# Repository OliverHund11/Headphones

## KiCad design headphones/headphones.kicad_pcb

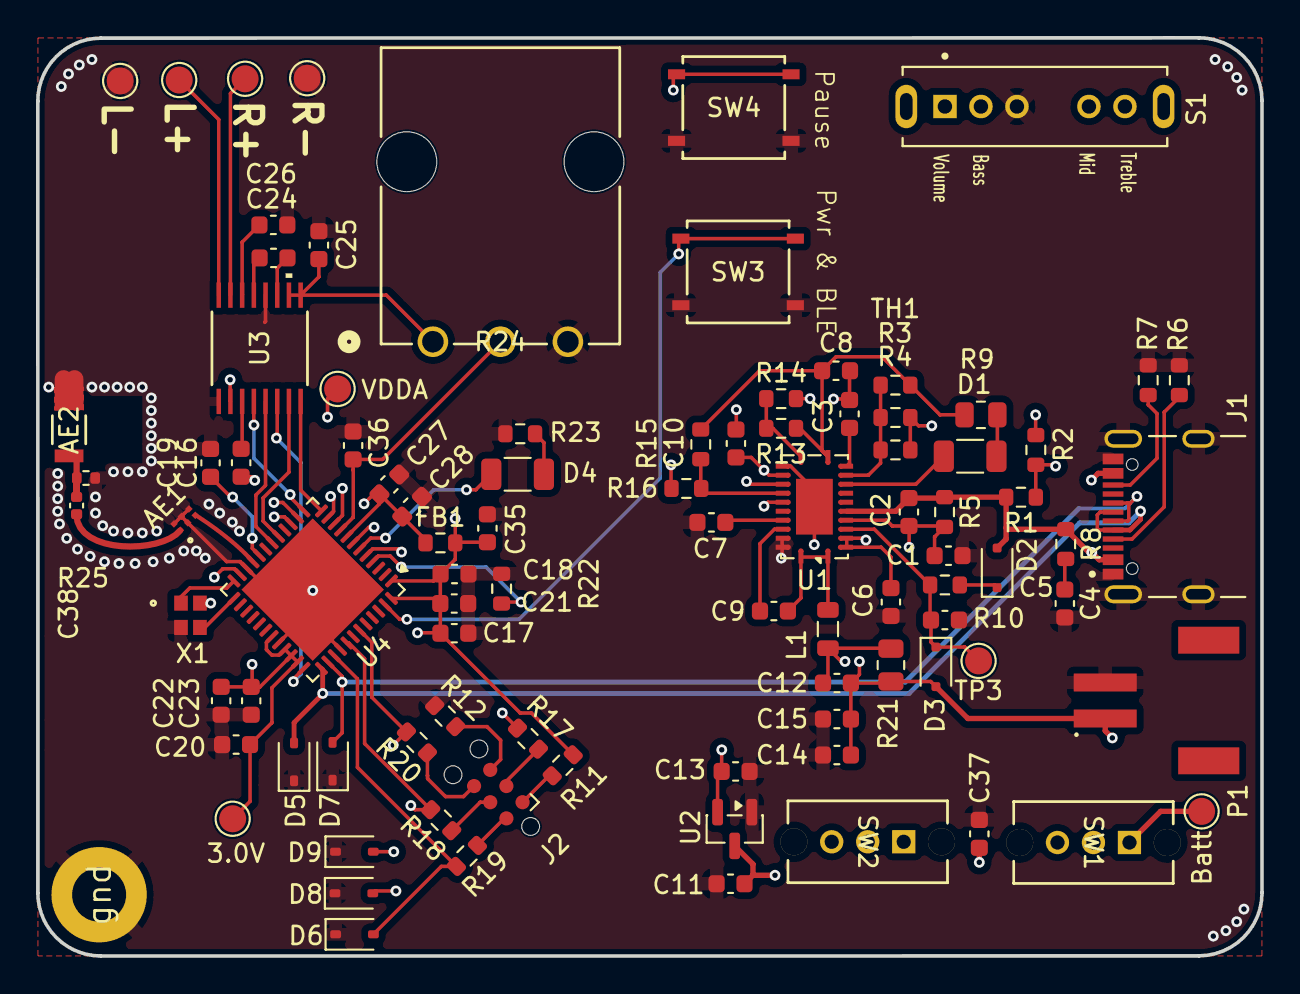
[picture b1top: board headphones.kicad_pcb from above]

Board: 4 copper layers, 68.0 x 51.0 mm, 93 parts (0 on the bottom side), 64 nets.

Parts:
3.0V: TestPoint; TestPoint_Pad_D1.5mm
AE1: MLPF-WB55-01E3; MLPF-WB55-01E3_STM
AE2: 2119640001; ANT_211964-0001_MOL
Batt: TestPoint; TestPoint_Pad_D1.5mm
C1, C2, C5, C10, C12: 0.1uF; C_0603_1608Metric
C3: 33nF; C_0603_1608Metric
C4, C16: 2.2uF; C_0603_1608Metric
C6, C14, C15: 10uF; C_0603_1608Metric
C7, C8, C11, C13, C37: 1uF; C_0603_1608Metric
C9: 0.047uF; C_0603_1608Metric
C17: 10u; C_0603_1608Metric
C18, C19, C20, C21, C22, C23, C36: 0.1u; C_0603_1608Metric
C24: 220nF; C_0603_1608Metric
C25, C26: 4.7uF; C_0603_1608Metric
C27: 10n; C_0603_1608Metric
C28, C35: 1u; C_0603_1608Metric
C38: 2.7pF; C_0402_1005Metric
D1: LED, R; R_1206_3216Metric
D2, D3: D_SOD-323F
D4: LED, O; R_1206_3216Metric
D5, D6, D7, D8, D9: SD03CQ_SOD323; D_SOD-323
FB1: 120R; R_0603_1608Metric
J1: UJ20-C-H-G-SMT-1-P16-TR; SAMESKY_UJ20-C-H-G-SMT-1-P16-TR
J2: Conn_ARM_SWD_TagConnect_TC2030-NL; Tag-Connect_TC2030-IDC-NL_2x03_P1.27mm_Vertical
L1: 10uH; L_0805_2012Metric
P1: S2B-PH-SM4-TB
R1: 47k; R_0603_1608Metric
R2: 15k; R_0603_1608Metric
R3, R6, R7: 5.1k; R_0603_1608Metric
R4: 30k; R_0603_1608Metric
R5: 20m; R_0603_1608Metric
R8: 2; R_0603_1608Metric
R9: 750; R_0805_2012Metric
R10: 5; R_0603_1608Metric
R11, R12, R17, R18, R19, R20: 150; R_0603_1608Metric
R13: 13k; R_0603_1608Metric
R14: 1k; R_0603_1608Metric
R15: 8.2k; R_0603_1608Metric
R16: 56k; R_0603_1608Metric
R21: 47m; R_0805_2012Metric
R22: 10k; R_0603_1608Metric
R23: 330; R_0603_1608Metric
R24: P120PK-Y25BR10K; POT_P120PK-x25_TTE
R25: 0; R_0402_1005Metric
S1: SLW-1478144-5A-S-D; SW_SLW-1478144-5A-S-D
SW1, SW2: OS102011MS2QN1; SPDT_OS102011_CNK
SW3, SW4: SW_MEC_5E; SON4_PTS526 SM15 SMTR2 LFS_CNK
TH1: 10k; R_0603_1608Metric
TP3: TestPoint; TestPoint_Pad_D1.5mm
TP8: +LDriver; TestPoint_Pad_D1.5mm
TP9: -LDriver; TestPoint_Pad_D1.5mm
TP10: +RDriver; TestPoint_Pad_D1.5mm
TP11: -RDriver; TestPoint_Pad_D1.5mm
U1: BQ24133RGY; Texas_RGY_R-PVQFN-N24_EP2.05x3.1mm
U2: AP2127N-3.0; SOT-23
U3: NAU8402WG; TSSOP16_NAU8402_NUV
U4: STM32WB55CCUx; QFN-48-1EP_7x7mm_P0.5mm_EP5.6x5.6mm
VDDA: TestPoint; TestPoint_Pad_D1.5mm
X1: NX2016SA-32MHZ-EXS00A-CS06654; NX2016SA_NDK
gnd: (no value)

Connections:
+3.0V: 3.0V.1 (1_1), C13.2, C17.1, C18.1, C19.1, C20.1, C21.1, C22.1, C23.1, C25.1, C35.1, FB1.2, R11.2, R24.1, U2.2 (VO), U3.9 (VDDB), U3.10 (LINEVDD), U4.1 (VBAT), U4.20 (VDD), U4.23 (VDDRF), U4.31 (VFBSMPS), U4.33 (VLXSMPS), U4.34 (VDDSMPS), U4.35 (VDD), U4.48 (VDD)
+3.3V, ref: C8.2, R3.1, R9.2, R13.1, R15.1, U1.12 (VREF)
+5V: C2.1, D2.2 (A), J1.A4_B9 (VBUS), J1.B4_A9 (VBUS__1), R1.1, R5.1, R8.1, SW1.3, U1.6 (ACP)
+BATT: Batt.1 (1_1), C10.2, C12.2, C14.2, C15.2, D3.2 (A), P1.1, R21.2, SW1.1, U1.15 (SRN)
/Bass: S1.2, U4.11 (PA2)
/D+: D7.2 (A2), J1.A6 (DP1), J1.B6 (DP2), U4.38 (PA12)
/D-: D5.2 (A2), J1.A7 (DN1), J1.B7 (DN2), U4.37 (PA11)
/Lsig: TP8.1 (1_1), U3.16 (LLINEOU)
/Mid: S1.5, U4.14 (PA5)
/Mute: U3.4 (MUTEB), U4.13 (PA4)
/NRST: R17.2, U4.7 (NRST)
/PVCC: C1.1, C2.2, C6.1, R5.2, U1.2 (PVCC), U1.3 (PVCC), U1.5 (ACN)
/Rsig: TP10.1 (1_1), U3.15 (RLINEOUT)
/SAI_FS: U3.5 (FS), U4.18 (PA9)
/SAI_MCLK: U3.8 (MCLK), U4.12 (PA3)
/SAI_SCK: U3.7 (BCLK), U4.17 (PA8)
/SAI_SD: U3.6 (DACIN), U4.36 (PA10)
/SWCLK: D8.2 (A2), R18.2, U4.41 (PA14)
/SWDIO: D6.2 (A2), R19.2, U4.39 (PA13)
/SWO: D9.2 (A2), R20.2, U4.43 (PB3)
/Treble: S1.6, U4.15 (PA6)
/Volume: S1.1, U4.10 (PA1)
GND: AE1.A2 (GND4), AE1.B1 (GND3), AE1.B2 (GND2), AE1.B3 (GND1), AE2.2, C1.2, C4.2, C5.2, C6.2, C7.1, C11.1, C13.1, C14.1, C15.1, C16.1, C17.2, C18.2, C19.2, C20.2, C21.2, C22.2, C23.2, C25.2, C26.2, C27.2, C28.2, C35.2, C36.2, C37.1, D5.1 (A1), D6.1 (A1), D7.1 (A1), D8.1 (A1), D9.1 (A1), J1.A1_B12 (GND), J1.B1_A12 (GND__1), J1.SH1 (SHIELD), J1.SH2 (SHIELD__1), J1.SH3 (SHIELD__2), J1.SH4 (SHIELD__3), P1.2, R6.2, R7.2, R12.1, R22.1, R23.2, R24.3, R25.2, S1.3, SW3.3 (K), SW3.4 (A), SW4.3 (K), SW4.4 (A), TP9.1 (1_1), TP11.1 (1_1), U1.22 (PGND), U1.23 (PGND), U2.1 (GND), U3.1 (VSSA), U3.12 (LINEGND), U4.22 (VSSRF), U4.32 (VSSSMPS), U4.40 (VDDUSB), U4.49 (VSS), X1.2, X1.4, gnd.1
GNDREF: C3.2, C8.1, C10.1, R2.2, R4.2, R14.2, R16.2, TH1.2, U1.14 (CELL), U1.25 (AGND)
unnamed: AE1.A3 (IN), U4.21 (RF1)
unnamed: AE1.A1 (OUT), C38.1
unnamed: AE2.1 (1_1), C38.2, R25.1
unnamed: C4.1, R8.2
unnamed: C9.1, L1.1, U1.1 (SW), U1.24 (SW)
unnamed: C37.2, SW1.2, SW2.2
unnamed: D1.2 (A), R9.1
unnamed: D1.1 (K), U1.9 (STAT)
unnamed: D2.1 (K), R10.1
unnamed: C5.1, D3.1 (K), R10.2, TP3.1 (1_1), U1.4 (AVCC)
unnamed: D4.2 (A), U4.6 (PB9)
unnamed: D4.1 (K), R23.1
unnamed: J1.A5 (CC1), R6.1
unnamed: J1.B5 (CC2), R7.1
unnamed: J2.5 (GND), R12.2
unnamed: J2.4 (SWCLK), R18.1
unnamed: J2.2 (SWDIO), R19.1
unnamed: J2.6 (SWO), R20.1
unnamed: J2.1 (VCC), R11.1
unnamed: J2.3 (~RESET), R17.1
unnamed: R15.2, R16.1, U1.17 (ACSET)
unnamed: C9.2, U1.21 (BTST)
unnamed: R13.2, R14.1, U1.13 (ISET)
unnamed: R1.2, R2.1, U1.18 (OVPSET)
unnamed: C7.2, U1.20 (REGN)
unnamed: C12.1, L1.2, R21.1, U1.16 (SRP)
unnamed: R3.2, R4.1, TH1.1, U1.10 (TS)
unnamed: C3.1, U1.11 (TTC)
unnamed: C11.2, SW2.3, U2.3 (VI)
unnamed: C24.2, U3.11 (CPCA)
unnamed: C24.1, U3.13 (CPCB)
unnamed: C26.1, U3.14 (CPOUT)
unnamed: C16.2, U3.3 (VREF)
unnamed: U4.25 (OSC_IN), X1.3
unnamed: U4.24 (OSC_OUT), X1.1
unnamed: C36.1, R24.2, U4.9 (PA0)
unnamed: SW3.1, SW3.2, U4.47 (PB7)
unnamed: SW4.1, SW4.2, U4.5 (PB8)
unnamed: R22.2, U4.4 (PH3)
VDDA: C27.1, C28.1, FB1.1, U3.2 (VDDA), U4.8 (VDDA), VDDA.1 (1_1)
